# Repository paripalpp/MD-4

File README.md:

# MD-4
4th gen motor driver. some of them work but others not work. I couldn't find its cause.

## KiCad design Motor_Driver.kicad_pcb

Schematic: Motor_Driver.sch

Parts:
C1, C2: 0.1u; C_0603_1608Metric
C3, C4, C5, C6, C7, C8: 10u; C_0805_2012Metric
D1, D2: LED; LED_0603_1608Metric
D3, D4, D5, D6, D7, D8, D9, D10, D11, D12: D; D_SOD-123W
J1: Conn_01x04_Male; PinHeader_1x04_P2.54mm_Horizontal_Mirror
J2: Conn_01x40_Male; PinHeader_2x20_P2.54mm_Horizontal_Mirror
J3: Conn_01x02_Female; T_connecter_female_horizontal
Q1, Q2, Q3, Q4: Q_NMOS_SGD; TSON_Advance
R1, R2: 330; R_0603_1608Metric
R3, R4: 20kR; R_0603_1608Metric
R5, R7, R9, R11: 7.5R; R_0603_1608Metric
R6, R8, R10, R12: 10kR; R_0603_1608Metric
U1: NJM7812; TO-252-2
U2, U3: Si8274(DFN-14); DFN-14_4.9x4.9mm_P0.65mm

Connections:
+3V3: C1.1, C2.1, J1.1, U2.3, U2.5, U2.8, U3.3, U3.5, U3.8
+12V: C4.1, C5.1, C6.1, D3.2 (A), D4.2 (A), U1.3 (OUT), U2.11, U3.11
GND: C1.2, C2.2, J1.4, R1.2, R2.2, R3.2, R4.2, U2.4, U3.4
GNDPWR: C3.2, C4.2, C5.2, C6.2, D10.2 (A), D12.2 (A), J2.21, J2.22, J2.23, J2.24, J2.25, J2.26, J2.27, J2.28, J2.29, J2.30, J2.31, J2.32, J2.33, J2.34, J2.35, J2.36, J2.37, J2.38, J2.39, J2.40, Q2.1 (S), Q4.1 (S), R8.1, R12.1, U1.2 (GND), U2.9, U3.9
HG_1: D5.2 (A), Q1.2 (G), R5.1
HG_2: D7.2 (A), Q3.2 (G), R9.1
Hi_1: D5.1 (K), R5.2, R6.2, U2.15
Hi_2: D7.1 (K), R9.2, R10.2, U3.15
LG_1: D6.2 (A), Q2.2 (G), R7.1
LG_2: D8.2 (A), Q4.2 (G), R11.1
Low_1: D6.1 (K), R7.2, R8.2, U2.10
Low_2: D8.1 (K), R11.2, R12.2, U3.10
unnamed: D1.1 (K), R1.1
unnamed: D2.1 (K), R2.1
unnamed: R3.1, U2.6
unnamed: R4.1, U3.6
Out_1: C7.2, D9.2 (A), D10.1 (K), J3.2, Q1.1 (S), Q2.3 (D), R6.1, U2.14
Out_2: C8.2, D11.2 (A), D12.1 (K), J3.1, Q3.1 (S), Q4.3 (D), R10.1, U3.14
PWM1: D1.2 (A), J1.2, U2.1
PWM2: D2.2 (A), J1.3, U3.1
VB_1: C7.1, D3.1 (K), U2.16
VB_2: C8.1, D4.1 (K), U3.16
VCC: C3.1, D9.1 (K), D11.1 (K), J2.1, J2.2, J2.3, J2.4, J2.5, J2.6, J2.7, J2.8, J2.9, J2.10, J2.11, J2.12, J2.13, J2.14, J2.15, J2.16, J2.17, J2.18, J2.19, J2.20, Q1.3 (D), Q3.3 (D), U1.1 (IN)

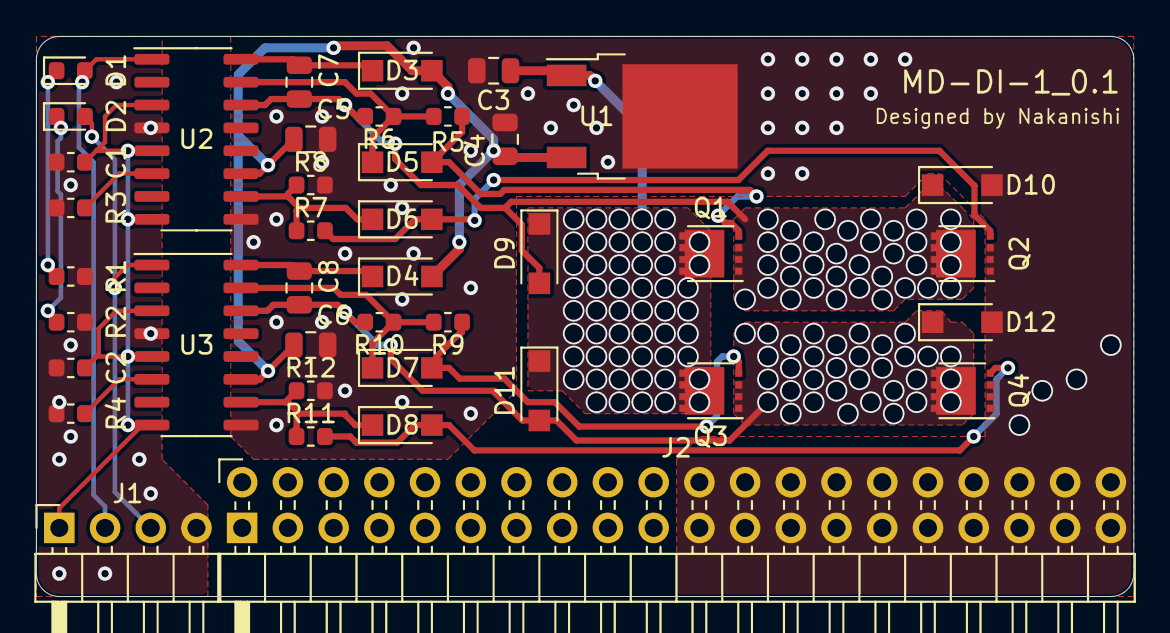
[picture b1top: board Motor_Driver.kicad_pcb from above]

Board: 2 copper layers, 61.0 x 31.1 mm, 42 parts (1 on the bottom side), 23 nets.

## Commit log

2021-12-17 0.1 first
